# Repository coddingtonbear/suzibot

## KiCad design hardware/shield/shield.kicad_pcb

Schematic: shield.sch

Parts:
C1, C2: 22p; C_0805_HandSoldering
C3: 0.01u; C_0805_HandSoldering
C4: 22u; C_Radial_D5_L6_P2.5
C5, C6, C7, C8: 0.1u; C_0805_HandSoldering
D1: ORANGE; LED_0805
D2: RED; LED_0805
D3: BLUE; LED_0805
E1: JNHUAMAO_HM-10; JNHUAMAO_26.9X13X2.2_BOARD
J10: USB_OTG; USB_Mini-B
JP1, JP2: Pin_Header_Straight_1x03
PA0, PA1: DP_DEVICES.V6_M1X8
PB0, PB1: DP_DEVICES.V6_M1X8
PC0, PC1: DP_DEVICES.V6_M1X8
PD0, PD1: DP_DEVICES.V6_M1X8
PROG0, PROG1: DP_DEVICES.V6_M1X6
PWR0, PWR1, PWR2, PWR3: DP_DEVICES.V6_M1X3
R1: 68; R_0805_HandSoldering
R2: 150; R_0805_HandSoldering
R3: 100; R_0805_HandSoldering
R4: DTR-RST; C_0805
R5: RTS-RST; C_0805
R6: 3V3USB; C_0805
SW1: RESET; NANO-SWITCH
U1: LM1117; SPARKFUN-POWERIC_SOT223
U2: 74LV4052; SOIC-16_3.9x9.9mm_Pitch1.27mm
U3: TXB0104; SOIC-14_3.9x8.7mm_Pitch1.27mm
U$1: CH340G_SOIC16
Y1: 12M; Crystal_HC49-U_Vertical

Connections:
/3V3: C7.1, E1.11 (RESET), E1.12 (+3.3V), JP1.1, JP2.1, R6.2, U1.2 (OUT), U1.4 (OUT), U3.1 (VA), U3.8 (OE)
/CONN-BT: E1.24 (LED), U3.5 (A4)
/D-: J10.2 (D-), U$1.6 (D-)
/DTR: PROG0.1, PROG1.1, R4.2, R5.2, SW1.1, U3.11 (B3)
/DTR-BT: E1.25 (PIO2), U3.4 (A3)
/DTR-USB: R4.1, U$1.13 (DTR)
/N$2: JP1.3, JP2.3, PWR0.2, PWR1.2, R1.1
/N$6: J10.1 (VBUS), PROG0.4, PROG1.4
/N$8: C3.2, R6.1, U$1.4 (V3)
/N$9: PD0.8, PD1.8
/N$10: PD0.7, PD1.7
/N$11: PD0.6, PD1.6
/N$12: PD0.5, PD1.5
/N$13: PD0.4, PD1.4
/N$14: PD0.3, PD1.3
/N$15: PD0.2, PD1.2
/N$16: PD0.1, PD1.1
/N$17: PC0.8, PC1.8
/N$18: PC0.7, PC1.7
/N$19: PC0.6, PC1.6
/N$20: PROG0.5, PROG1.5
/N$21: PC0.4, PC1.4, R3.2, U2.10 (A0), U3.10 (B4)
/N$22: PC0.3, PC1.3
/N$23: PC0.2, PC1.2
/N$24: PC0.1, PC1.1
/N$25: PB0.8, PB1.8
/N$26: PB0.7, PB1.7
/N$27: PB0.6, PB1.6
/N$28: PB0.5, PB1.5
/N$29: PB0.4, PB1.4
/N$30: PB0.3, PB1.3
/N$31: PB0.2, PB1.2
/N$32: PB0.1, PB1.1
/N$33: PA0.8, PA1.8
/N$34: PA0.7, PA1.7
/N$35: PA0.6, PA1.6
/N$36: PA0.5, PA1.5
/N$37: PA0.4, PA1.4
/N$38: PA0.3, PA1.3
/N$39: PA0.2, PA1.2
/N$40: PA0.1, PA1.1
/N$44: JP1.2, PWR3.2
/N$45: JP2.2, PWR2.2
/PB: PC0.5, PC1.5
/RX: PROG0.2, PROG1.2, U2.13 (X)
/RXD-CH340G: U2.12 (X0), U$1.3 (RX)
/TX: PROG0.3, PROG1.3, U2.3 (Y)
/TXD-CH340G: U2.1 (Y0), U$1.2 (TX)
/XI: C1.1, U$1.7 (XI), Y1.2
/XO: C2.1, U$1.8 (XO), Y1.1
D+: J10.3 (D+), U$1.5 (D+)
GND: C1.2, C2.2, C3.1, C4.2, C5.2, C6.2, C7.2, C8.2, D1.1 (K), D2.1 (K), D3.1 (K), E1.13 (GND), E1.14 (GND), E1.21 (GND), E1.22 (GND), J10.5 (GND), PROG0.6, PROG1.6, PWR0.1, PWR1.1, PWR2.1, PWR3.1, U1.1 (ADJ), U2.6 (~E), U2.7 (VEE), U2.8 (Vss), U2.9 (A1), U3.7 (GND), U$1.1 (GND)
unnamed: D1.2 (A), R1.2
unnamed: D2.2 (A), R2.2
unnamed: D3.2 (A), R3.1
unnamed: E1.1 (UART_TX), U3.2 (A1)
unnamed: E1.2 (UART_RX), U3.3 (A2)
unnamed: R5.1, U$1.14 (RTS)
unnamed: U2.5 (Y1), U3.13 (B1)
unnamed: U2.14 (X1), U3.12 (B2)
Vdd: C4.1, C5.1, C6.1, C8.1, PWR0.3, PWR1.3, PWR2.3, PWR3.3, R2.1, SW1.2, U1.3 (IN), U2.16 (Vdd), U3.14 (VB), U$1.16 (VCC)

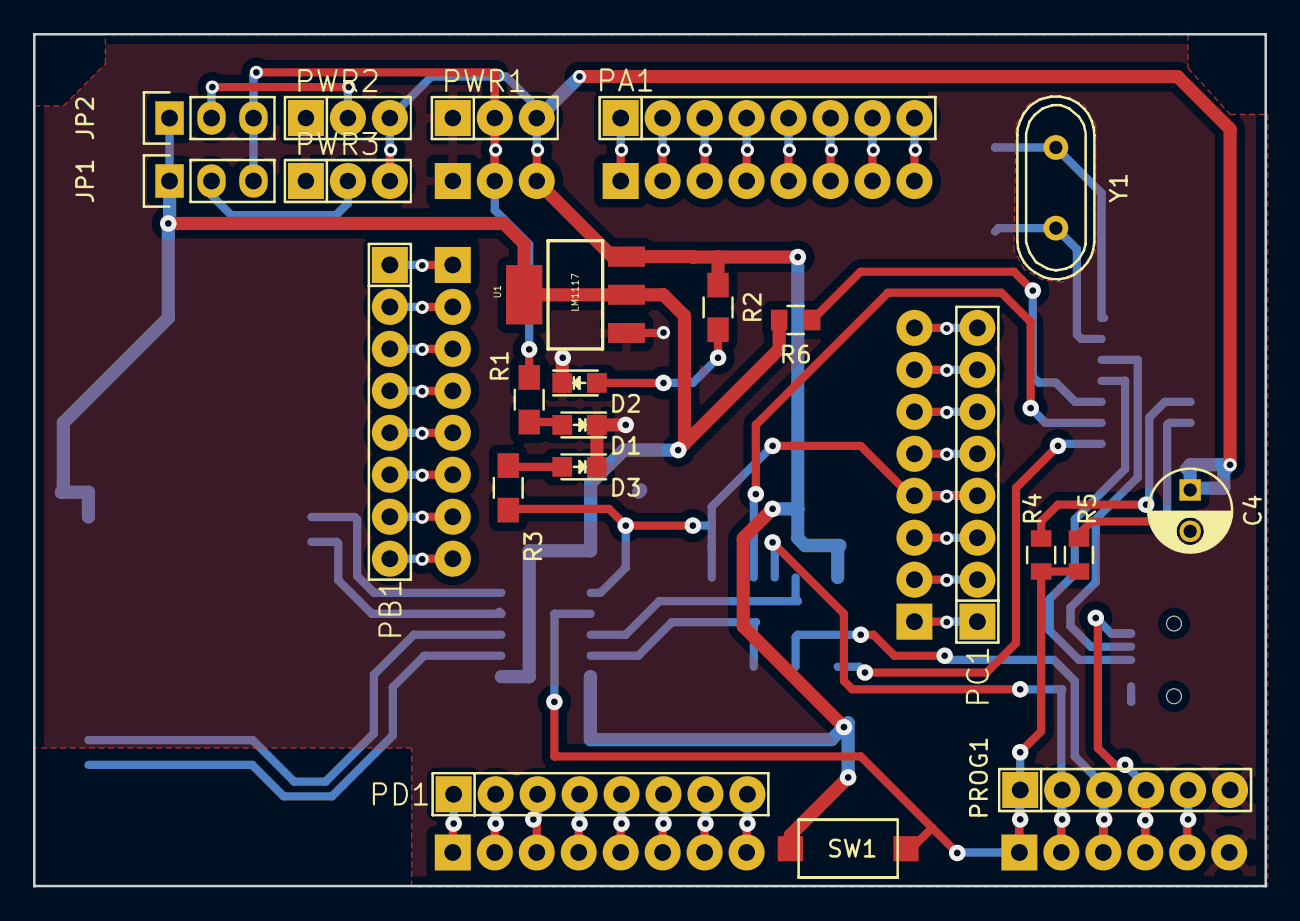
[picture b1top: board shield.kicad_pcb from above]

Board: 2 copper layers, 74.5 x 51.6 mm, 41 parts (0 on the bottom side), 61 nets.

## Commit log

2016-09-26 And so it begins.
2016-09-26 Adding software, too.
2016-09-26 Moving software into the right folder.
2016-09-28 Latest attempts.
2016-09-29 More attempts.
2016-10-01 Another iteration.
2016-10-02 Totally working. IT WAS VOLTAGE LEVELS AND CRYSTAL CAPACITANCE PROBLEMS ALL ALONG.
2016-10-07 Basic working features.
2016-10-08 Adding a ground plane at @nbanerje's suggestion. Thanks @nbanerje!
2016-10-08 Minor changes to improve positioning.
2016-10-08 Some routing alterations; fixing SD card package sizing.
2016-10-08 Routing a bunch of wires further from the pins.
2016-10-08 Adding some text.
2016-10-09 Updating board and schematic.
2016-10-09 Updating generated PDFs.
2016-10-10 Updating board.
2016-10-10 Moving voltage sensor slightly closer to edge.
2016-10-10 Updating software.
2016-10-16 SMD-ized; pre-autorouting.
2016-10-17 Fully layed-out.
2016-10-17 Updating to include missing connection to Vout.
2016-10-17 Adding LED to PB1 (per https://www.flickr.com/photos/maniacbug/6413368937/)
2016-11-01 Updating to v1.3 boardfile (what was once an atmega328p is now an atmega1284p)
2016-11-02 Breaking out various functions into their own cpp/h files.
2016-11-04 Updating each subservice to use a class with a generic interface.
2016-11-04 Inherit from a standard class to enforce interface matching.
2016-11-07 Much better decoupling; adding TI TPS2113A for limiting inrush current.
2016-11-08 Start board with 3V3 rail disabled; enable after ~1s (long enough for caps to charge)
2016-11-08 Remove dependence upon ESP8266.
2016-11-08 Add assertion/deassertion of SPI bus for SD card interactions.
2016-11-08 Adding 1k pullup resistor for disabling 3V3 regulator until MC-enabled.
2016-11-28 Updating to include EventManager.
2016-11-30 Minor build changes; switching back to high-speed SPI.
2016-11-30 Minor changes to timing and cleanup.
2016-11-30 Updating to latest board version.
2016-11-30 Switch to pin names rather than using artificially-assigned mightycore pin numbers.
2016-11-30 Adding ArduinoJson and EventManager.
2016-12-03 Applying some new knowledge from @KateGregory's C++ introduction course.
2016-12-04 Switching from .ino format to .cpp/.h
2016-12-04 3s is enough, apparently.
2016-12-04 Converting EventManager to instead accept a String* to allow for JSON responses.
2016-12-05 Working event bus.
2016-12-05 Adding code for incrementally building buffers for wifimanager.
2016-12-05 Adding basic callback workflow for WifiManager.
2016-12-06 Move LED lighting into system manager.
2016-12-07 Adding some structure.
2016-12-21 Adding new 'suzibot-shield' subproject.
2016-12-22 New version of shield.
2016-12-22 Fully-routed; just the wrong size.
2016-12-23 Fully routed and with parts in reasonably OK spots.
2016-12-24 Fully working; switched to USB MINI B.
